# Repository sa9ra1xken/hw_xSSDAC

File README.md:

https://youtube.com/shorts/RJUZ4uOECH0?feature=share

This is a KiCad project for an experimental implementation of a digital audio device that features an XMOS xCORE embedded processor.
The board is intended to behave as a USB audio class output device (USB DAC), or an audio media player (Micro SD card player). 
Please refer to [project Wiki page](https://github.com/sa9ra1xken/hw_xSSDAC/wiki) for more detailed information.

# Development Environment
KiCad7.0. 

### Software project
Software (executable on xCORE-200) for this project is released here (https://github.com/sa9ra1xken/sw_xSSDAC).

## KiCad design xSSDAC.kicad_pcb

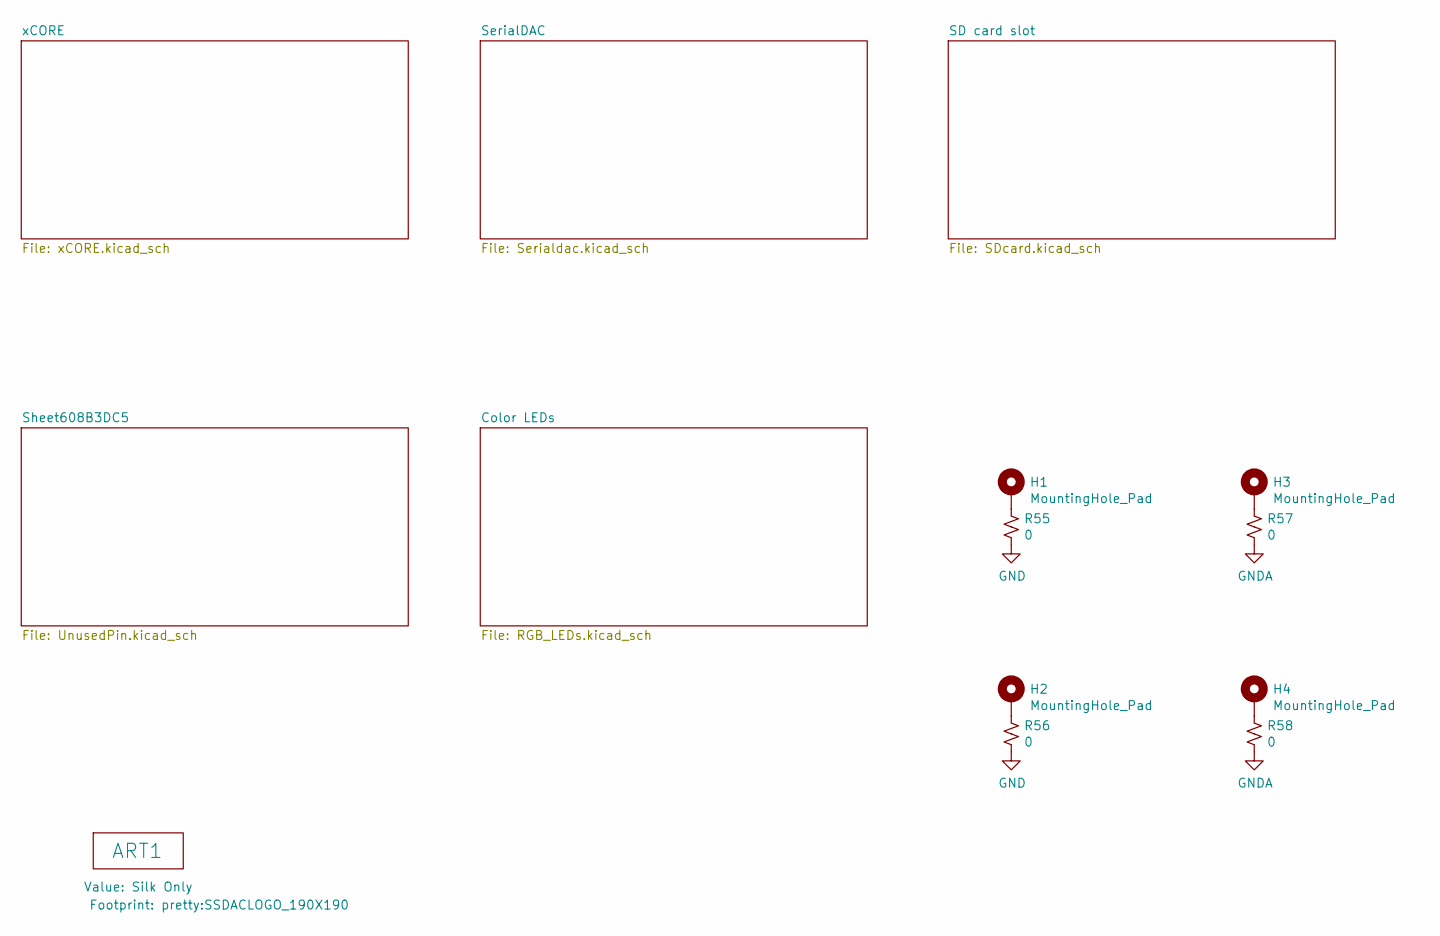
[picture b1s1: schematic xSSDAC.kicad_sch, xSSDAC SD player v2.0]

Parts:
ART1: Silk Only; SSDACLOGO_190X190
H1, H2, H3, H4: MountingHole_Pad; MountingHole_2.7mm_Pad_Via
R55, R56, R57, R58: 0; R_0603_1608Metric_Pad0.98x0.95mm_HandSolder

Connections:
GNDA: R57.2, R58.2; also elsewhere on the board
unnamed: H1.1, R55.1
unnamed: H2.1, R56.1
unnamed: H3.1, R57.1
unnamed: H4.1, R58.1

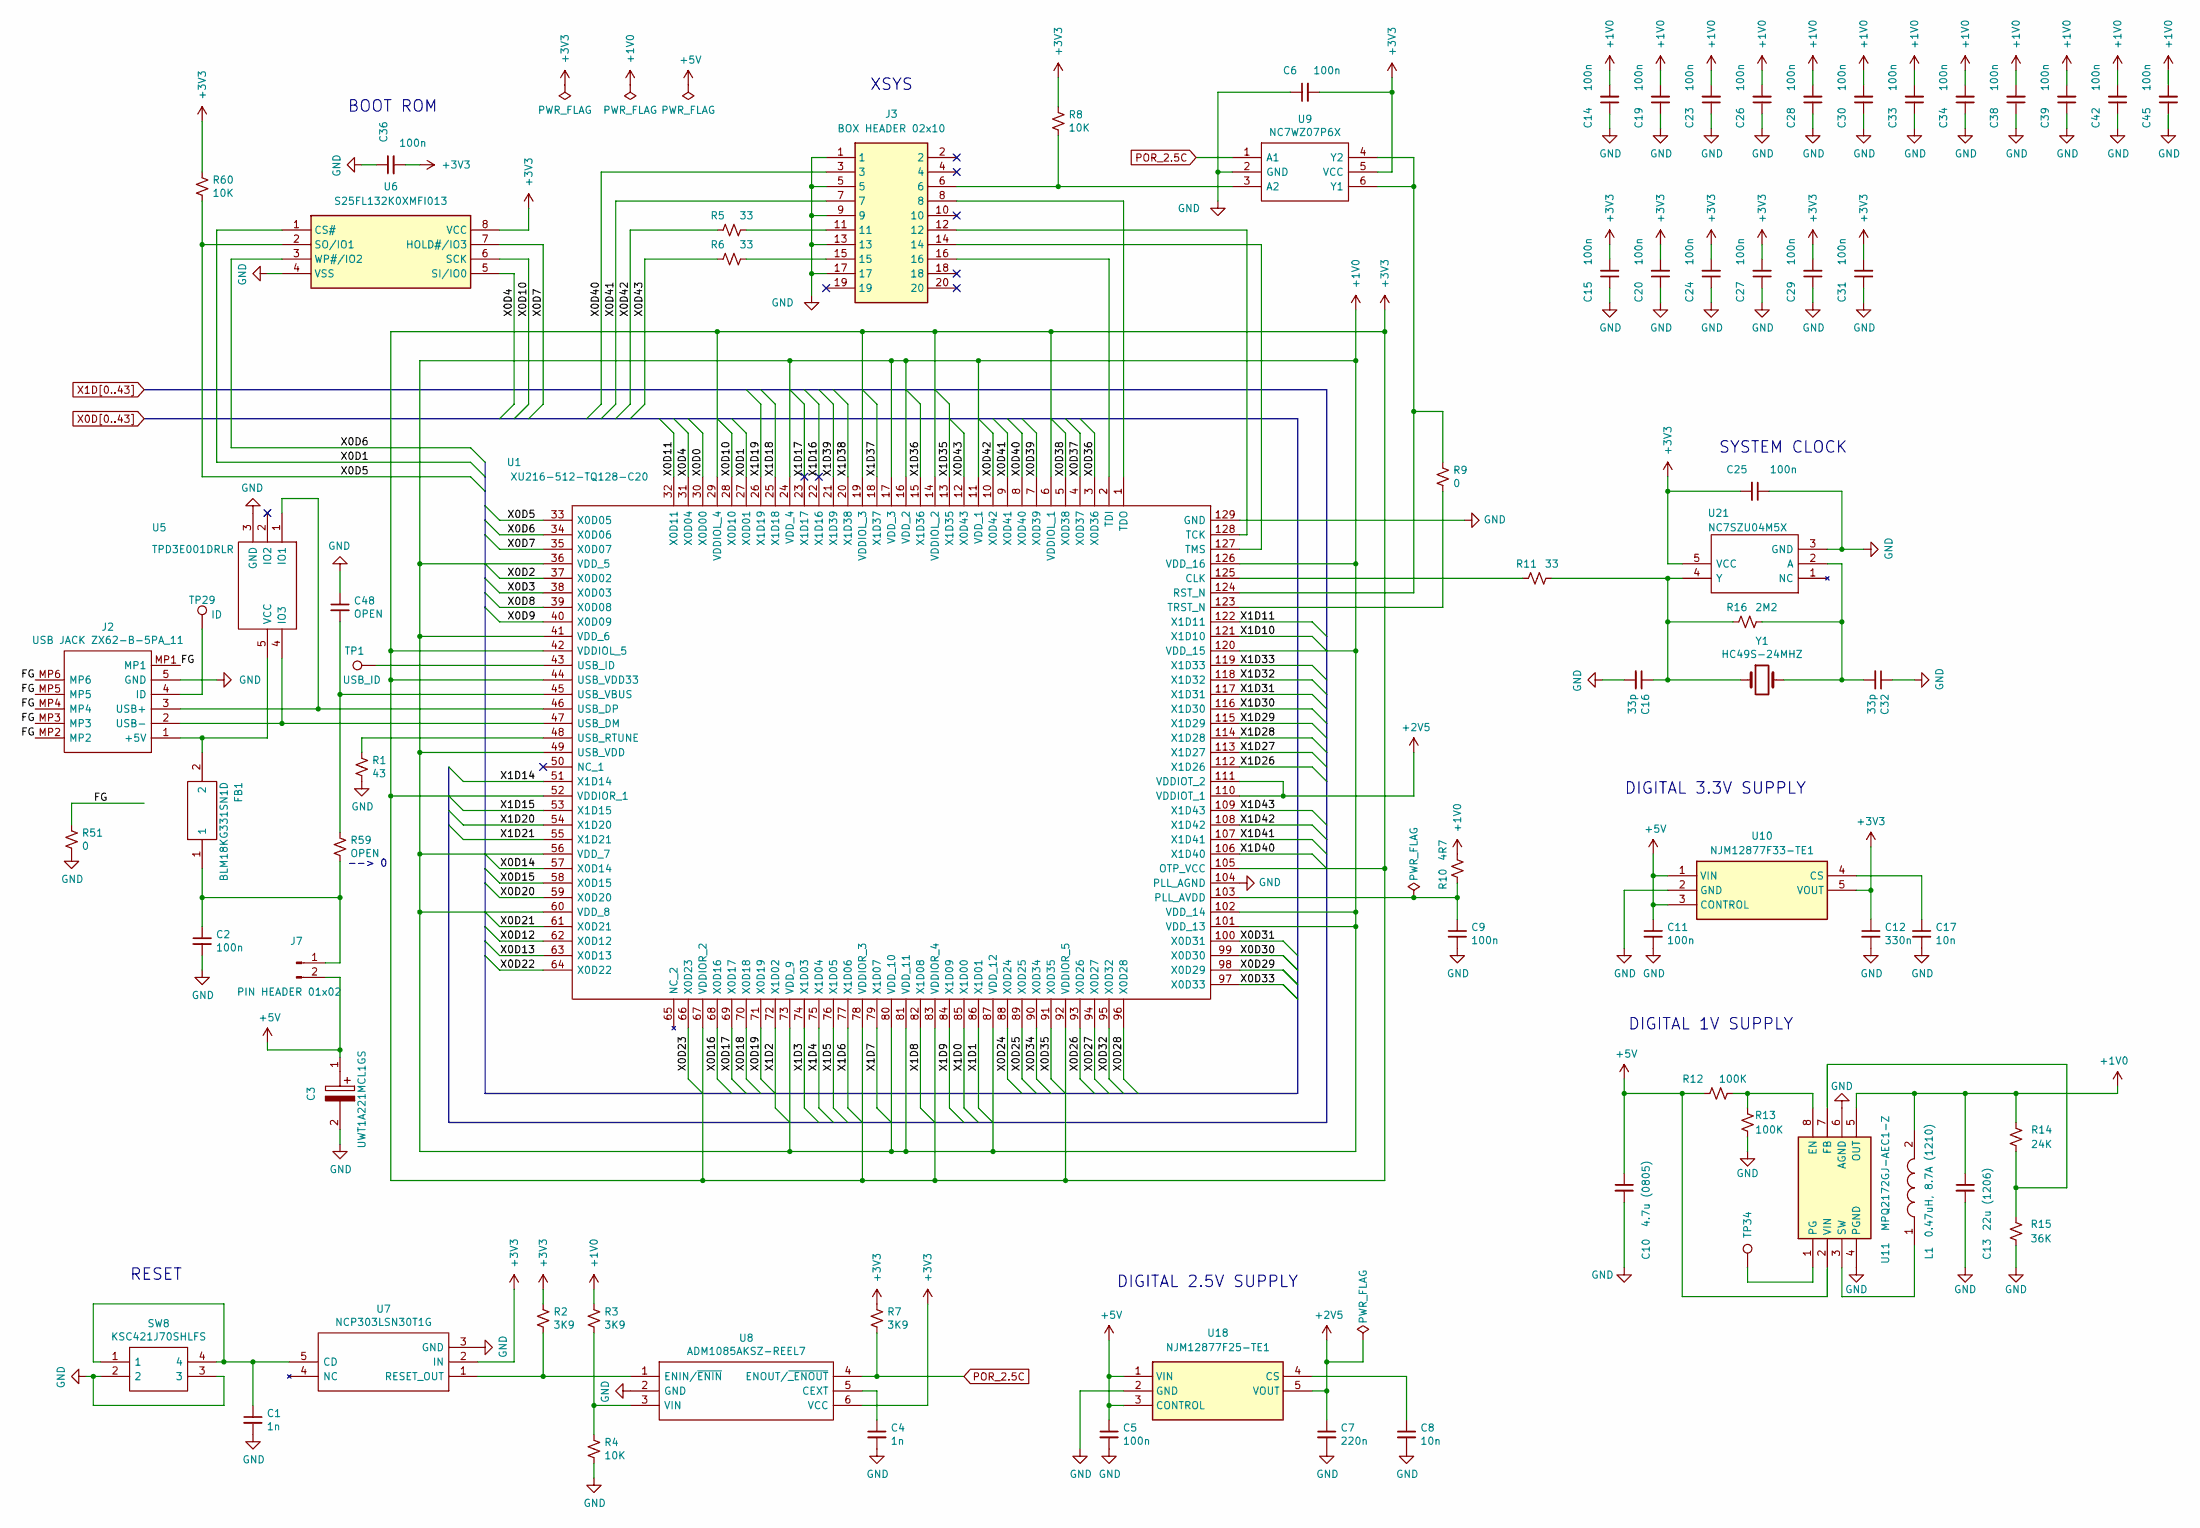
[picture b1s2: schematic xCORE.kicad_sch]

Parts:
C1, C4: 1n; C_0603_1608Metric_Pad1.08x0.95mm_HandSolder
C2, C5, C6, C9, C11, C14, C15, C19, C20, C23, C24, C25, C26, C27, C28, C29, C30, C31, C33, C34, C36, C38, C39, C42, C45: 100n; C_0603_1608Metric_Pad1.08x0.95mm_HandSolder
C3: UWT1A221MCL1GS; CP_Elec_6.3x7.7; Manufacturer_Part_Number UWT1A221MCL1GS; Mouser Part Number 647-UWT1A221MCL1GS
C7: 220n; C_0603_1608Metric_Pad1.08x0.95mm_HandSolder
C8, C17: 10n; C_0603_1608Metric_Pad1.08x0.95mm_HandSolder
C10: 4.7u (0805); C_0805_2012Metric_Pad1.18x1.45mm_HandSolder
C12: 330n; C_0603_1608Metric_Pad1.08x0.95mm_HandSolder
C13: 22u (1206); C_1206_3216Metric_Pad1.33x1.80mm_HandSolder
C16, C32: 33p; C_0603_1608Metric_Pad1.08x0.95mm_HandSolder
C48: OPEN; C_0603_1608Metric_Pad1.08x0.95mm_HandSolder
FB1: BLM18KG331SN1D; BEADC1608X95N; Manufacturer_Part_Number BLM18KG331SN1D; Mouser Part Number 81-BLM18KG331SN1D
J2: USB JACK ZX62-B-5PA_11; ZX62B5PA; Mouser Part Number 798-ZX62-B-5PA11
J3: BOX HEADER 02x10; SHDRRA20W66P254_2X10_3289X986X927P; Manufacturer_Part_Number 5103310-5; Mouser Part Number 571-5103310-5
J7: PIN HEADER 01x02; PinHeader_1x02_P2.54mm_Vertical
L1: 0.47uH, 8.7A (1210); L_1210_3225Metric_Pad1.42x2.65mm_HandSolder; Manufacturer_Part_Number DFE32CAHR47MR0; Mouser Part Number 963-NR10050T4R9N
R1: 43; R_0603_1608Metric_Pad0.98x0.95mm_HandSolder
R2, R3, R7: 3K9; R_0603_1608Metric_Pad0.98x0.95mm_HandSolder
R4, R8, R60: 10K; R_0603_1608Metric_Pad0.98x0.95mm_HandSolder
R5, R6, R11: 33; R_0603_1608Metric_Pad0.98x0.95mm_HandSolder
R9, R51: 0; R_0603_1608Metric_Pad0.98x0.95mm_HandSolder
R10: 4R7; R_0603_1608Metric_Pad0.98x0.95mm_HandSolder
R12, R13: 100K; R_0603_1608Metric_Pad0.98x0.95mm_HandSolder
R14: 24K; R_0603_1608Metric_Pad0.98x0.95mm_HandSolder
R15: 36K; R_0603_1608Metric_Pad0.98x0.95mm_HandSolder
R16: 2M2; R_0603_1608Metric_Pad0.98x0.95mm_HandSolder
R59: OPEN; R_0603_1608Metric_Pad0.98x0.95mm_HandSolder
SW8: KSC421J70SHLFS; KSC401G50SHLFS; Manufacturer_Part_Number KSC421J70SHLFS; Mouser Part Number 611-KSC421J70SHLFS
TP1: USB_ID; TestPoint_Pad_D1.0mm_noCrtYd
TP29: ID; TestPoint_Pad_D1.0mm_noCrtYd
TP34: TestPoint; TestPoint_Pad_D1.0mm_noCrtYd
U1: XU216-512-TQ128-C20; QFP40P1600X1600X120-129N-D; Manufacturer_Part_Number XU216-512-TQ128-C20; DigiKey Part Number 880-1118-ND
U5: TPD3E001DRLR; SOTFL50P160X60-5N; Mouser Part Number 595-TPD3E001DRLR
U6: S25FL132K0XMFI013; SOIC127P800X216-8N; Manufacturer_Part_Number S25FL132K0XMFI013
U7: NCP303LSN30T1G; SOT95P280X145-5N; Manufacturer_Part_Number NCP303LSN30T1G; Mouser Part Number 863-NCP303LSN30T1G
U8: ADM1085AKSZ-REEL7; SOT65P210X110-6N; Manufacturer_Part_Number ADM1085AKSZ-REEL7; Mouser Part Number 584-ADM1085AKSZ-R7
U9: NC7WZ07P6X; SOT65P210X110-6N; Manufacturer_Part_Number NC7WZ07P6X; Mouser Part Number 512-NC7WZ07P6X
U10: NJM12877F33-TE1; SOT-23-5_HandSoldering; Manufacturer_Part_Number NJM12877F33-TE1; Mouser Part Number 513-NJM12877F33-TE1
U11: MPQ2172GJ-AEC1-Z; MPQ2172GJAEC1Z; Manufacturer_Part_Number MPQ2172GJ-AEC1-Z
U18: NJM12877F25-TE1; SOT-23-5_HandSoldering; Manufacturer_Part_Number NJM12877F33-TE1; Mouser Part Number 513-NJM12877F33-TE1
U21: NC7SZU04M5X; SOT95P280X145-5N; Manufacturer_Part_Number NC7SZU04M5X; Mouser Part Number 512-NC7SZU04M5X
Y1: HC49S-24MHZ; Crystal_HC49-U_Vertical; Manufacturer_Part_Number HC49/U-S24000000ABJB

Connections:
+2V5: C7.1, U1.110 (VDDIOT_1), U1.111 (VDDIOT_2), U18.5 (VOUT)
/xCORE/FG: J2.MP1, J2.MP2, J2.MP3, J2.MP4, J2.MP5, J2.MP6, R51.1
unnamed: FB1.2, J2.1 (+5V), U5.5 (VCC)
unnamed: J2.4 (ID), TP29.1
unnamed: J2.3 (USB+), U1.46 (USB_DP), U5.1 (IO1)
unnamed: J2.2 (USB-), U1.47 (USB_DM), U5.4 (IO3)
unnamed: J3.11, R5.1
unnamed: J3.15, R6.1
unnamed: C2.1, FB1.1, J7.1, R59.2
unnamed: R11.2, U1.125 (CLK)
unnamed: C9.1, R10.2, U1.103 (PLL_AVDD)
unnamed: R9.1, U1.124 (RST_N), U9.4 (Y2), U9.6 (Y1)
unnamed: J3.12, U1.128 (TCK)
unnamed: J3.16, U1.2 (TDI)
unnamed: J3.8, U1.1 (TDO)
unnamed: J3.14, U1.127 (TMS)
unnamed: R9.2, U1.123 (TRST_N)
unnamed: TP1.1, U1.43 (USB_ID)
unnamed: R1.1, U1.48 (USB_RTUNE)
unnamed: C48.2, R59.1, U1.45 (USB_VBUS)
unnamed: C1.1, SW8.1, SW8.4, U7.5 (CD)
unnamed: R2.2, U7.1 (RESET_OUT), U8.1 (ENIN/~ENIN)
unnamed: C4.1, U8.5 (CEXT)
unnamed: R3.2, R4.1, U8.3 (VIN)
unnamed: J3.6, R8.2, U9.3 (A2)
unnamed: C17.1, U10.4 (CS)
unnamed: R12.2, R13.2, U11.8 (EN)
unnamed: R14.2, R15.2, U11.7 (FB)
unnamed: L1.1, U11.3 (SW)
unnamed: C8.1, U18.4 (CS)
unnamed: C32.2, R16.1, U21.2 (A), Y1.2
unnamed: C16.1, R11.1, R16.2, U21.4 (Y), Y1.1
POR_2.5C: R7.2, U8.4 (ENOUT/~_ENOUT), U9.1 (A1)
X0D0: U1.30 (X0D00); also elsewhere on the board
X0D1: U1.27 (X0D01), U6.1 (CS#)
X0D2: U1.37 (X0D02); also elsewhere on the board
X0D3: U1.38 (X0D03); also elsewhere on the board
X0D4: U1.31 (X0D04), U6.5 (SI/IO0)
X0D5: R60.2, U1.33 (X0D05), U6.2 (SO/IO1)
X0D6: U1.34 (X0D06), U6.3 (WP#/IO2)
X0D7: U1.35 (X0D07), U6.7 (HOLD#/IO3)
X0D8: U1.39 (X0D08); also elsewhere on the board
X0D9: U1.40 (X0D09); also elsewhere on the board
X0D10: U1.28 (X0D10), U6.6 (SCK)
X0D11: U1.32 (X0D11); also elsewhere on the board
X0D12: U1.62 (X0D12); also elsewhere on the board
X0D13: U1.63 (X0D13); also elsewhere on the board
X0D14: U1.57 (X0D14); also elsewhere on the board
X0D15: U1.58 (X0D15); also elsewhere on the board
X0D16: U1.68 (X0D16); also elsewhere on the board
X0D17: U1.69 (X0D17); also elsewhere on the board
X0D18: U1.70 (X0D18); also elsewhere on the board
X0D19: U1.71 (X0D19); also elsewhere on the board
X0D20: U1.59 (X0D20); also elsewhere on the board
X0D21: U1.61 (X0D21); also elsewhere on the board
X0D22: U1.64 (X0D22); also elsewhere on the board
X0D23: U1.66 (X0D23); also elsewhere on the board
X0D26: U1.93 (X0D26); also elsewhere on the board
X0D27: U1.94 (X0D27); also elsewhere on the board
X0D28: U1.96 (X0D28); also elsewhere on the board
X0D29: U1.98 (X0D29); also elsewhere on the board
X0D30: U1.99 (X0D30); also elsewhere on the board
X0D31: U1.100 (X0D31); also elsewhere on the board
X0D32: U1.95 (X0D32); also elsewhere on the board
X0D33: U1.97 (X0D33); also elsewhere on the board
X0D34: U1.90 (X0D34); also elsewhere on the board
X0D35: U1.91 (X0D35); also elsewhere on the board
X0D36: U1.3 (X0D36); also elsewhere on the board
X0D37: U1.4 (X0D37); also elsewhere on the board
X0D38: U1.5 (X0D38); also elsewhere on the board
X0D39: U1.7 (X0D39); also elsewhere on the board
X0D40: J3.3, U1.8 (X0D40)
X0D41: J3.7, U1.9 (X0D41)
X0D42: R5.2, U1.10 (X0D42)
X0D43: R6.2, U1.12 (X0D43)
X1D0: U1.85 (X1D00); also elsewhere on the board
X1D1: U1.86 (X1D01); also elsewhere on the board
X1D2: U1.72 (X1D02); also elsewhere on the board
X1D3: U1.74 (X1D03); also elsewhere on the board
X1D4: U1.75 (X1D04); also elsewhere on the board
X1D5: U1.76 (X1D05)
X1D6: U1.77 (X1D06)
X1D7: U1.79 (X1D07)
X1D8: U1.82 (X1D08); also elsewhere on the board
X1D9: U1.84 (X1D09); also elsewhere on the board
X1D10: U1.121 (X1D10); also elsewhere on the board
X1D11: U1.122 (X1D11); also elsewhere on the board
X1D14: U1.51 (X1D14)
X1D15: U1.53 (X1D15)
X1D16: U1.22 (X1D16)
X1D17: U1.23 (X1D17)
X1D18: U1.25 (X1D18)
X1D19: U1.26 (X1D19)
X1D20: U1.54 (X1D20)
X1D21: U1.55 (X1D21)
X1D26: U1.112 (X1D26); also elsewhere on the board
X1D27: U1.113 (X1D27); also elsewhere on the board
X1D28: U1.114 (X1D28); also elsewhere on the board
X1D29: U1.115 (X1D29); also elsewhere on the board
X1D30: U1.116 (X1D30); also elsewhere on the board
X1D31: U1.117 (X1D31); also elsewhere on the board
X1D32: U1.118 (X1D32); also elsewhere on the board
X1D33: U1.119 (X1D33); also elsewhere on the board
X1D35: U1.13 (X1D35); also elsewhere on the board
X1D36: U1.15 (X1D36); also elsewhere on the board
X1D37: U1.18 (X1D37); also elsewhere on the board
X1D38: U1.20 (X1D38); also elsewhere on the board
X1D39: U1.21 (X1D39); also elsewhere on the board
X1D40: U1.106 (X1D40); also elsewhere on the board
X1D41: U1.107 (X1D41); also elsewhere on the board
X1D42: U1.108 (X1D42); also elsewhere on the board
X1D43: U1.109 (X1D43); also elsewhere on the board

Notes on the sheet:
DIGITAL 3.3V SUPPLY
--> 0
DIGITAL 2.5V SUPPLY
XSYS
DIGITAL 1V SUPPLY
BOOT ROM
SYSTEM CLOCK
RESET

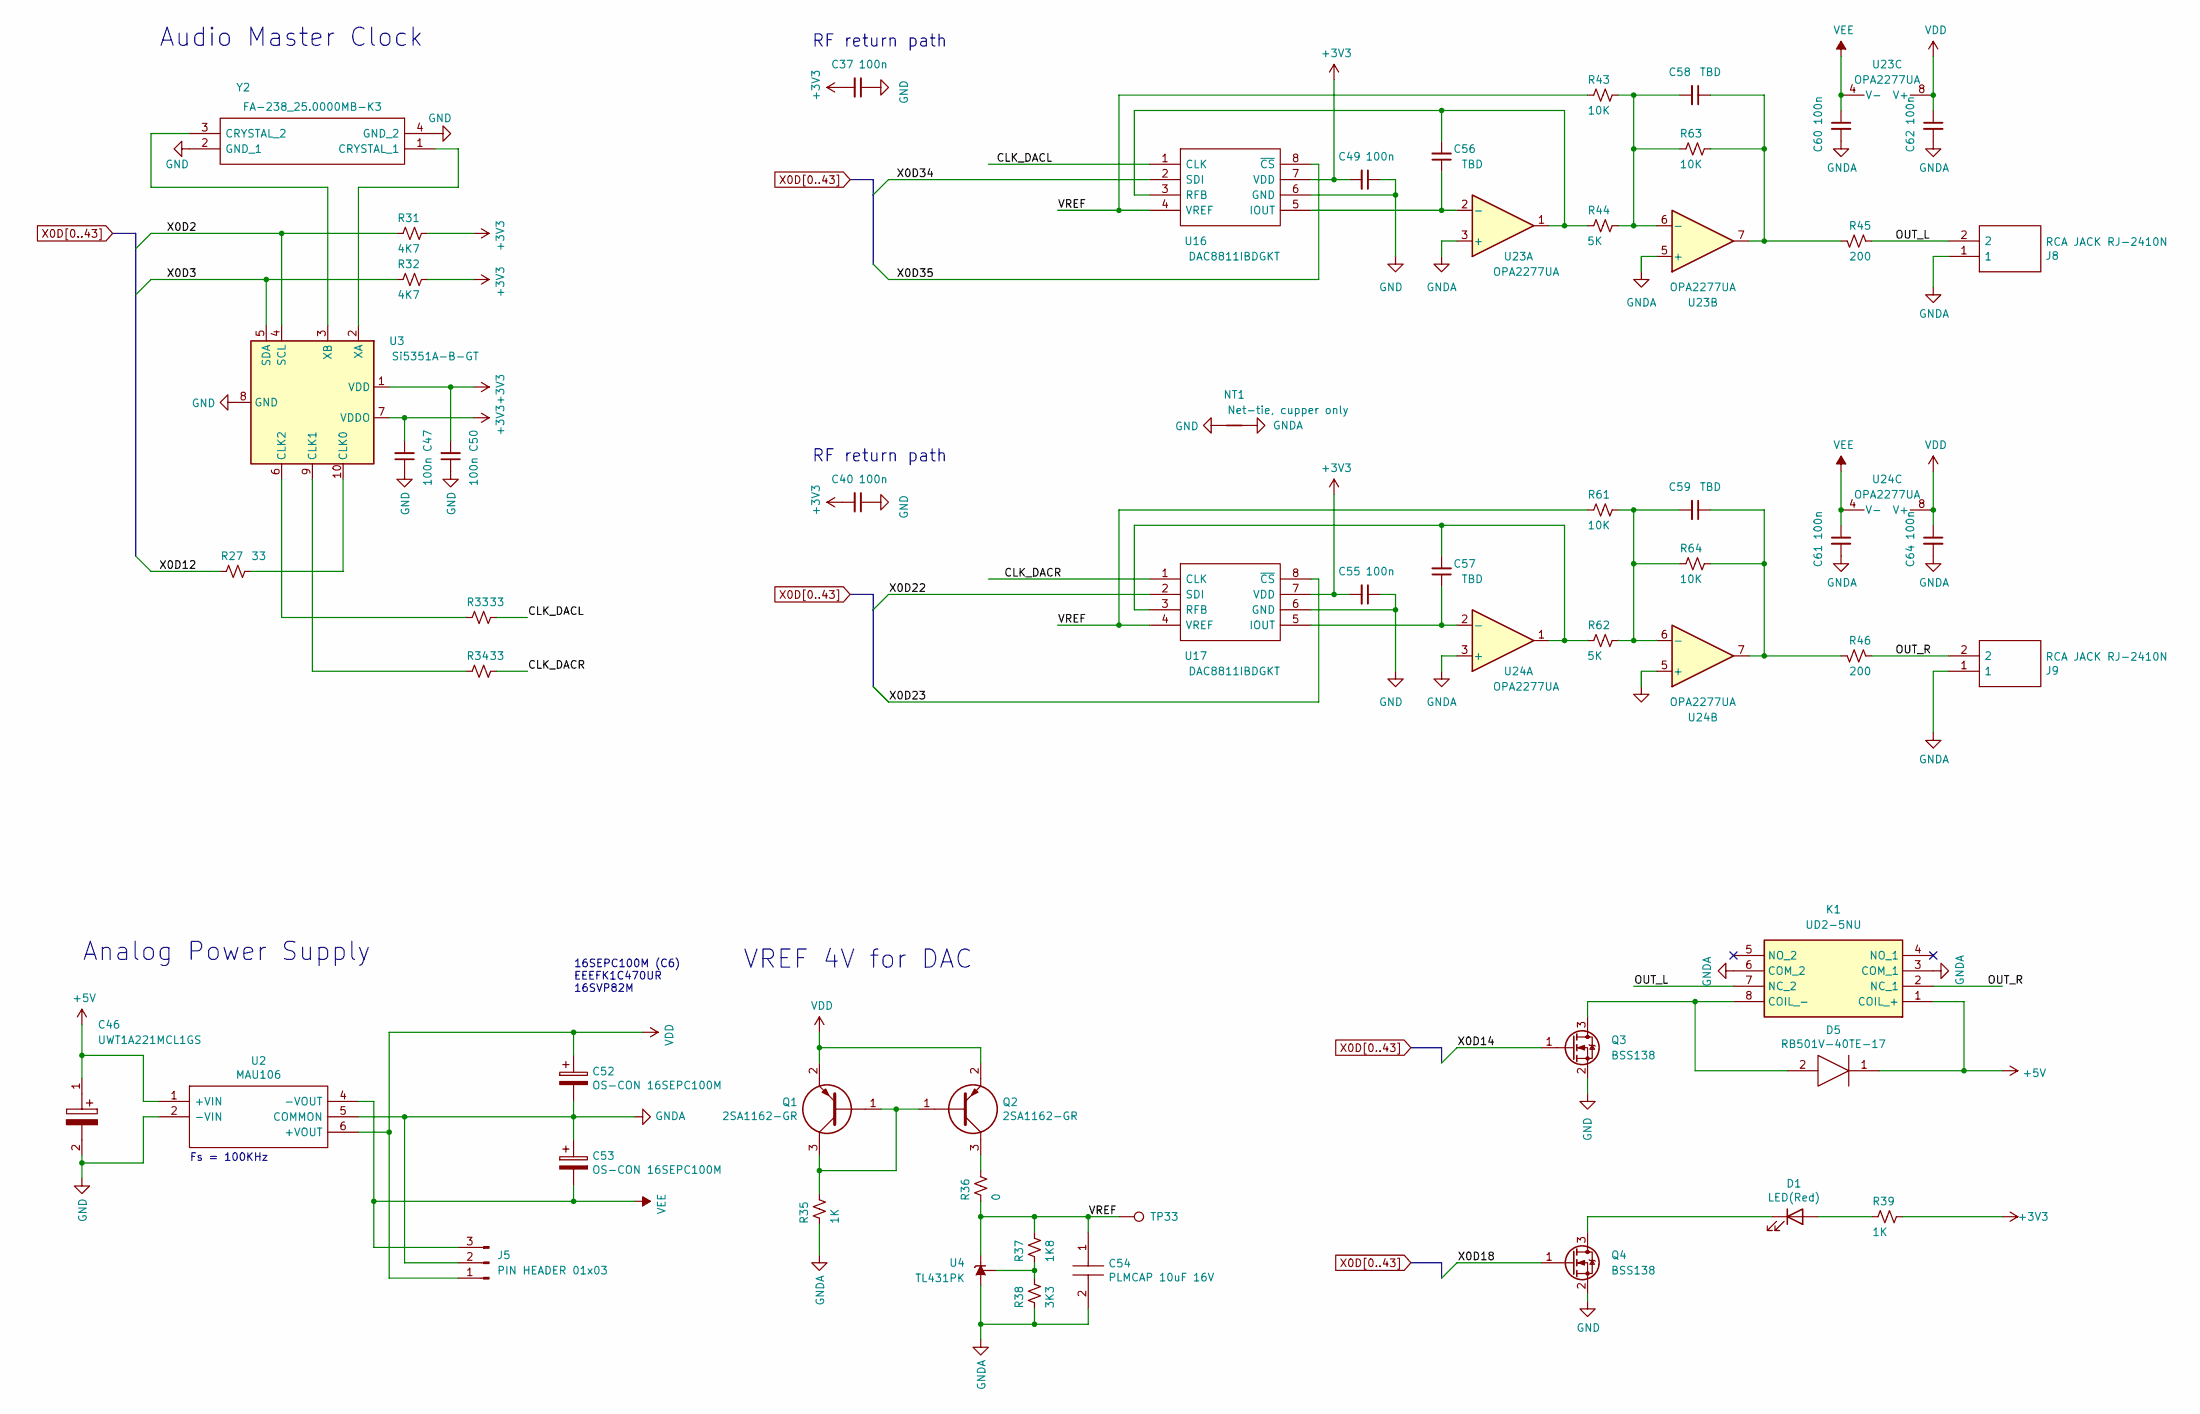
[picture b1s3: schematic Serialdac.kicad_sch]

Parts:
C37, C40, C47, C49, C50, C55, C60, C61, C62, C64: 100n; C_0603_1608Metric_Pad1.08x0.95mm_HandSolder
C46: UWT1A221MCL1GS; CP_Elec_6.3x7.7; Manufacturer_Part_Number UWT1A221MCL1GS; Mouser Part Number 647-UWT1A221MCL1GS
C52, C53: OS-CON 16SEPC100M; CP_Radial_D6.3mm_P2.50mm; Manufacturer_Part_Number OS-CON 16SEPC100M
C54: PLMCAP 10uF 16V; CAPC4532X280N; Manufacturer_Part_Number 16MU106MC44532; Mouser Part Number 232-16MU106MC44532
C56, C57, C58, C59: TBD; C_Rect_L4.0mm_W2.5mm_P2.50mm
D1: LED(Red); LED_0603_1608Metric_Pad1.05x0.95mm_HandSolder; Manufacturer_Part_Number OSHR1608C1A
D5: RB501V-40TE-17; SODFL2512X90N; Manufacturer_Part_Number RB501V-40TE-17; Mouser Part Number 755-RB501V-40TE-17
J5: PIN HEADER 01x03; PinHeader_1x03_P2.54mm_Vertical
J8, J9: RCA JACK RJ-2410N; RJ2410N; Manufacturer_Part_Number RJ-2410N
K1: UD2-5NU; UD25NUN; Manufacturer_Part_Number UD2-5NU; Mouser Part Number 551-UD2-5NU
NT1: Net-tie, cupper only; NetTie-2_SMD_Pad1.0mm
Q1, Q2: 2SA1162-GR; SC-59; Manufacturer_Part_Number 2SA1162-GR(F)
Q3, Q4: BSS138; SOT-23; Manufacturer_Part_Number BSS138
R27, R33, R34: 33; R_0603_1608Metric_Pad0.98x0.95mm_HandSolder
R31, R32: 4K7; R_0603_1608Metric_Pad0.98x0.95mm_HandSolder
R35, R39: 1K; R_0603_1608Metric_Pad0.98x0.95mm_HandSolder
R36: 0; R_0603_1608Metric_Pad0.98x0.95mm_HandSolder
R37: 1K8; R_0603_1608Metric_Pad0.98x0.95mm_HandSolder
R38: 3K3; R_0603_1608Metric_Pad0.98x0.95mm_HandSolder
R43, R61, R63, R64: 10K; R_Axial_DIN0204_L3.6mm_D1.6mm_P2.54mm_Vertical
R44, R62: 5K; R_Axial_DIN0204_L3.6mm_D1.6mm_P2.54mm_Vertical
R45, R46: 200; R_Axial_DIN0204_L3.6mm_D1.6mm_P2.54mm_Vertical
TP33: TestPoint; TestPoint_Pad_3.0x3.0mm
U2: MAU106; MAU109; Manufacturer_Part_Number MAU106
U3: Si5351A-B-GT; SOP50P490X110-10N; Manufacturer_Part_Number Si5351A-B-GT
U4: TL431PK; SOT-89-3; Manufacturer_Part_Number TA76431F
U16, U17: DAC8811IBDGKT; TSSOP-8_3x3mm_P0.65mm; Manufacturer_Part_Number DAC8811IBDGKT
U23, U24: OPA2277UA; SOIC-8_3.9x4.9mm_P1.27mm; Manufacturer_Part_Number OPA2277UA
Y2: FA-238_25.0000MB-K3; EPSON-FA-238; Manufacturer_Part_Number FA-238 25.0000MB-K3; Mouser Part Number 732-FA238-25B-K3

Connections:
/SerialDAC/CLK_DACL: R33.1, U16.1 (CLK)
/SerialDAC/CLK_DACR: R34.1, U17.1 (CLK)
/SerialDAC/OUT_L: J8.2, K1.7 (NC_2), R45.2
/SerialDAC/OUT_R: J9.2, K1.2 (NC_1), R46.2
GNDA: C52.2, C53.1, C54.2, C60.2, C61.2, C62.2, C64.2, J5.2, J8.1, J9.1, K1.3 (COM_1), K1.6 (COM_2), NT1.2, R35.2, R38.2, U2.5 (COMMON), U4.2 (A), U23.3 (+), U23.5 (+), U24.3 (+), U24.5 (+); also elsewhere on the board
unnamed: C58.1, R45.1, R63.2, U23.7
unnamed: C59.1, R46.1, R64.2, U24.7
unnamed: D5.2, K1.8 (COIL_-), Q3.3 (D)
unnamed: Q1.1, Q1.3, Q2.1, R35.1
unnamed: Q2.3, R36.1
unnamed: R27.1, U3.10 (CLK0)
unnamed: R34.2, U3.9 (CLK1)
unnamed: R33.2, U3.6 (CLK2)
unnamed: U3.2 (XA), Y2.1 (CRYSTAL_1)
unnamed: U3.3 (XB), Y2.3 (CRYSTAL_2)
unnamed: R37.2, R38.1, U4.1 (REF)
unnamed: C56.1, U16.5 (IOUT), U23.2 (-)
unnamed: C56.2, R44.1, U16.3 (RFB), U23.1
unnamed: C57.1, U17.5 (IOUT), U24.2 (-)
unnamed: C57.2, R62.1, U17.3 (RFB), U24.1
unnamed: C58.2, R43.2, R44.2, R63.1, U23.6 (-)
unnamed: C59.2, R61.2, R62.2, R64.1, U24.6 (-)
VDD: C52.1, C62.1, C64.1, J5.1, Q1.2, Q2.2, U2.6 (+VOUT), U23.8 (V+), U24.8 (V+)
VEE: C53.2, C60.1, C61.1, J5.3, U2.4 (-VOUT), U23.4 (V-), U24.4 (V-)
X0D2: R31.2, U3.4 (SCL); also elsewhere on the board
X0D3: R32.2, U3.5 (SDA); also elsewhere on the board
X0D12: R27.2; also elsewhere on the board
X0D14: Q3.1 (G); also elsewhere on the board
X0D22: U17.2 (SDI); also elsewhere on the board
X0D23: U17.8 (~CS); also elsewhere on the board
X0D34: U16.2 (SDI); also elsewhere on the board
X0D35: U16.8 (~CS); also elsewhere on the board

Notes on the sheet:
Fs = 100KHz
RF return path
VREF 4V for DAC
16SEPC100M (C6) EEEFK1C470UR 16SVP82M
Analog Power Supply
Audio Master Clock

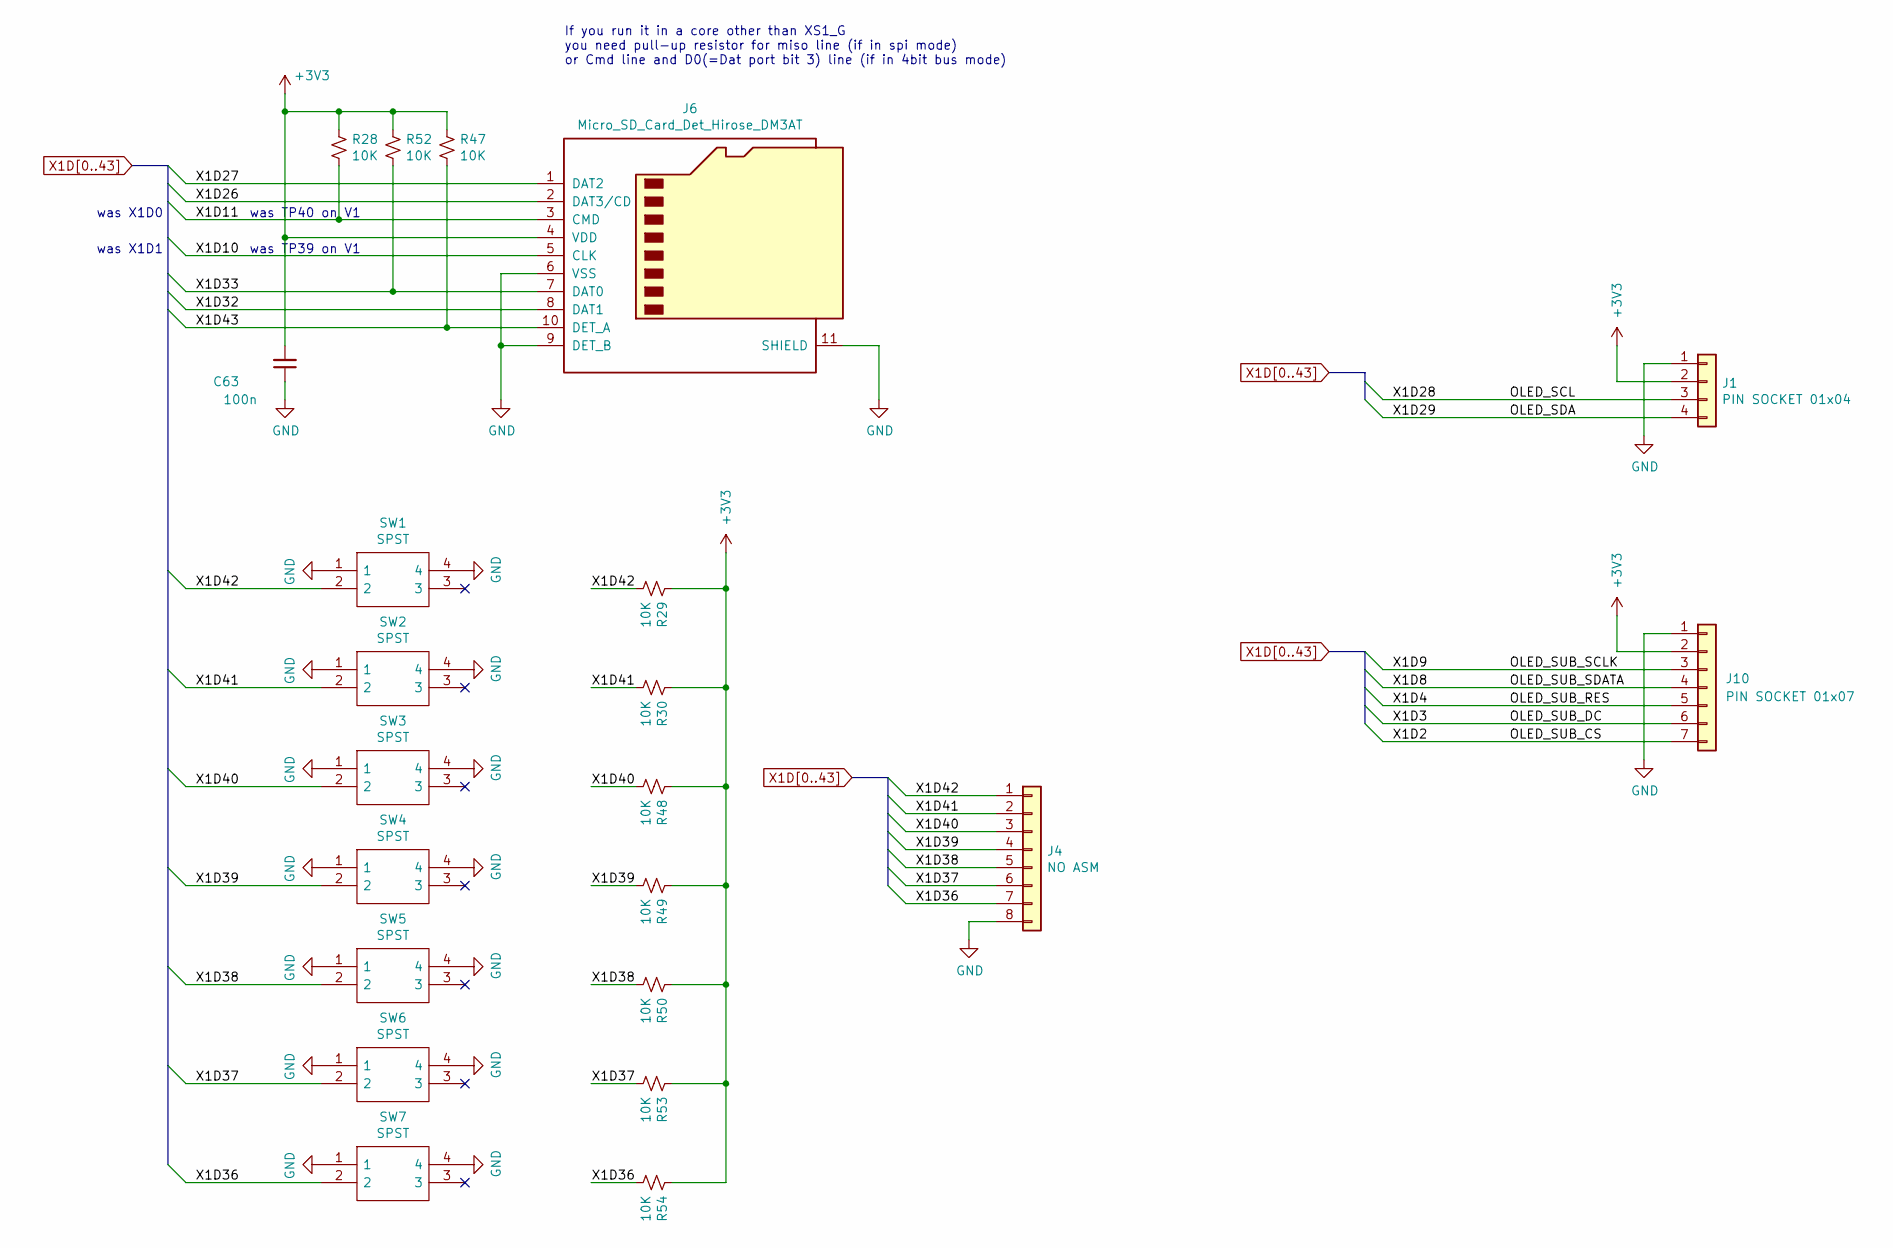
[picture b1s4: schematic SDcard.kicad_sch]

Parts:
C63: 100n; C_0603_1608Metric_Pad1.08x0.95mm_HandSolder
J1: PIN SOCKET 01x04; OLED_4pin_1.3_128X64
J4: NO ASM; PinHeader_1x08_P2.54mm_Vertical
J6: Micro_SD_Card_Det_Hirose_DM3AT; Hirose_DM3AT-SF-PEJM5
J10: PIN SOCKET 01x07; OLED_7pin_0.95_96X64_RGB
R28, R29, R30, R47, R48, R49, R50, R52, R53, R54: 10K; R_0603_1608Metric_Pad0.98x0.95mm_HandSolder
SW1, SW4, SW7: SPST; TS-0606; Manufacturer_Part_Number DTS-63-N-V-RED
SW2, SW3, SW5, SW6: SPST; TS-0606; Manufacturer_Part_Number DTS-63-N-V-WHT

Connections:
X1D2: J10.7; also elsewhere on the board
X1D3: J10.6; also elsewhere on the board
X1D4: J10.5; also elsewhere on the board
X1D8: J10.4; also elsewhere on the board
X1D9: J10.3; also elsewhere on the board
X1D10: J6.5 (CLK); also elsewhere on the board
X1D11: J6.3 (CMD), R28.2; also elsewhere on the board
X1D26: J6.2 (DAT3/CD); also elsewhere on the board
X1D27: J6.1 (DAT2); also elsewhere on the board
X1D28: J1.3; also elsewhere on the board
X1D29: J1.4; also elsewhere on the board
X1D32: J6.8 (DAT1); also elsewhere on the board
X1D33: J6.7 (DAT0), R52.2; also elsewhere on the board
X1D36: J4.7, R54.2, SW7.2; also elsewhere on the board
X1D37: J4.6, R53.2, SW6.2; also elsewhere on the board
X1D38: J4.5, R50.2, SW5.2; also elsewhere on the board
X1D39: J4.4, R49.2, SW4.2; also elsewhere on the board
X1D40: J4.3, R48.2, SW3.2; also elsewhere on the board
X1D41: J4.2, R30.2, SW2.2; also elsewhere on the board
X1D42: J4.1, R29.2, SW1.2; also elsewhere on the board
X1D43: J6.10 (DET_A), R47.2; also elsewhere on the board

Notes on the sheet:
was X1D0
was X1D1
was TP40 on V1
was TP39 on V1
If you run it in a core other than XS1_G you need pull-up resistor for miso line (if in spi mode) or Cmd line and D0(=Dat port bit 3) line (if in 4bit bus mode)

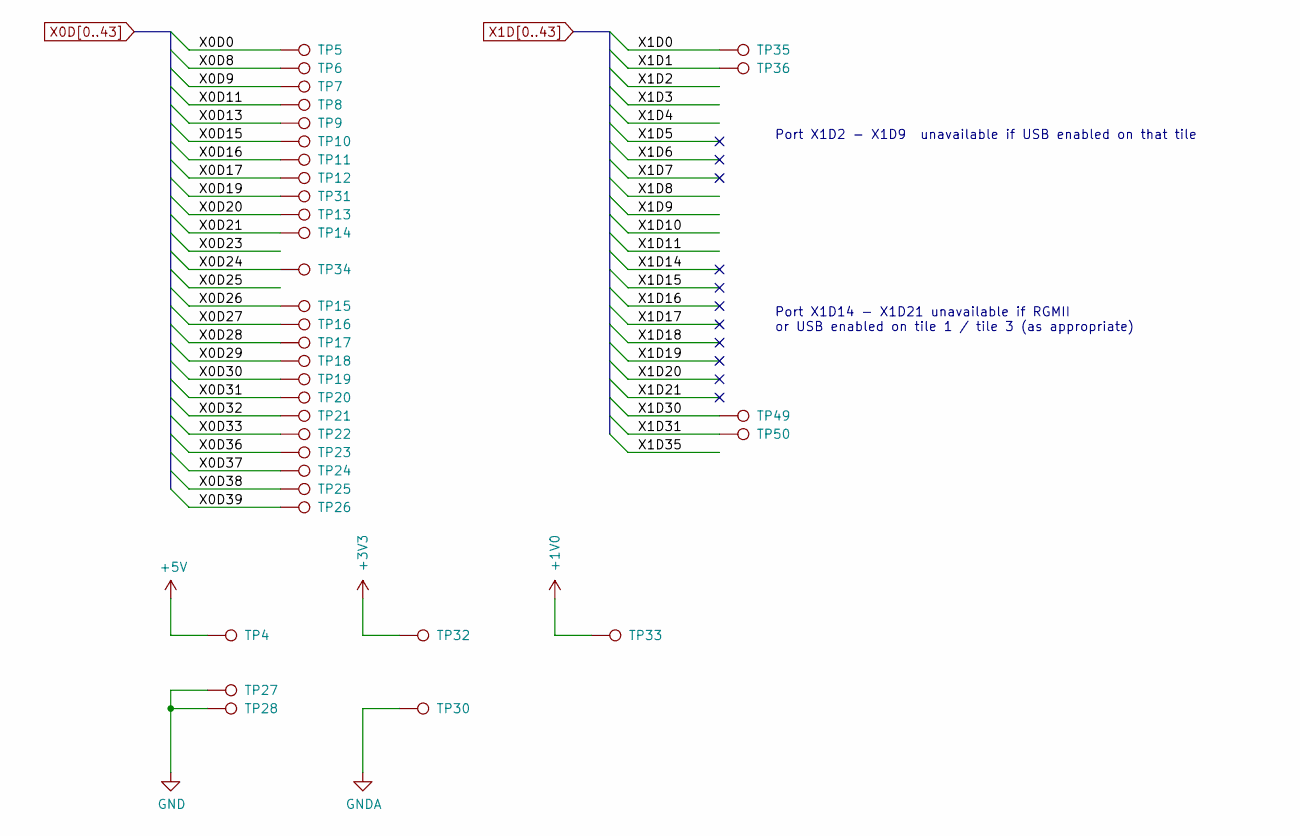
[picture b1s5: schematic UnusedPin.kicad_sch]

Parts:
TP4, TP27, TP28, TP30, TP32, TP33: TestPoint; TestPoint_Pad_3.0x3.0mm
TP5, TP6, TP7, TP8, TP9, TP10, TP11, TP12, TP13, TP14, TP15, TP16, TP17, TP18, TP19, TP20, TP21, TP22, TP23, TP24, TP25, TP26, TP31, TP34, TP35, TP36, TP49, TP50: TestPoint; TestPoint_Pad_D1.0mm_noCrtYd

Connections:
GNDA: TP30.1; also elsewhere on the board
X0D0: TP5.1; also elsewhere on the board
X0D8: TP6.1; also elsewhere on the board
X0D9: TP7.1; also elsewhere on the board
X0D11: TP8.1; also elsewhere on the board
X0D13: TP9.1; also elsewhere on the board
X0D15: TP10.1; also elsewhere on the board
X0D16: TP11.1; also elsewhere on the board
X0D17: TP12.1; also elsewhere on the board
X0D19: TP31.1; also elsewhere on the board
X0D20: TP13.1; also elsewhere on the board
X0D21: TP14.1; also elsewhere on the board
X0D26: TP15.1; also elsewhere on the board
X0D27: TP16.1; also elsewhere on the board
X0D28: TP17.1; also elsewhere on the board
X0D29: TP18.1; also elsewhere on the board
X0D30: TP19.1; also elsewhere on the board
X0D31: TP20.1; also elsewhere on the board
X0D32: TP21.1; also elsewhere on the board
X0D33: TP22.1; also elsewhere on the board
X0D36: TP23.1; also elsewhere on the board
X0D37: TP24.1; also elsewhere on the board
X0D38: TP25.1; also elsewhere on the board
X0D39: TP26.1; also elsewhere on the board
X1D0: TP35.1; also elsewhere on the board
X1D1: TP36.1; also elsewhere on the board
X1D30: TP49.1; also elsewhere on the board
X1D31: TP50.1; also elsewhere on the board

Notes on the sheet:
Port X1D2 - X1D9 unavailable if USB enabled on that tile
Port X1D14 - X1D21 unavailable if RGMII or USB enabled on tile 1 / tile 3 (as appropriate)

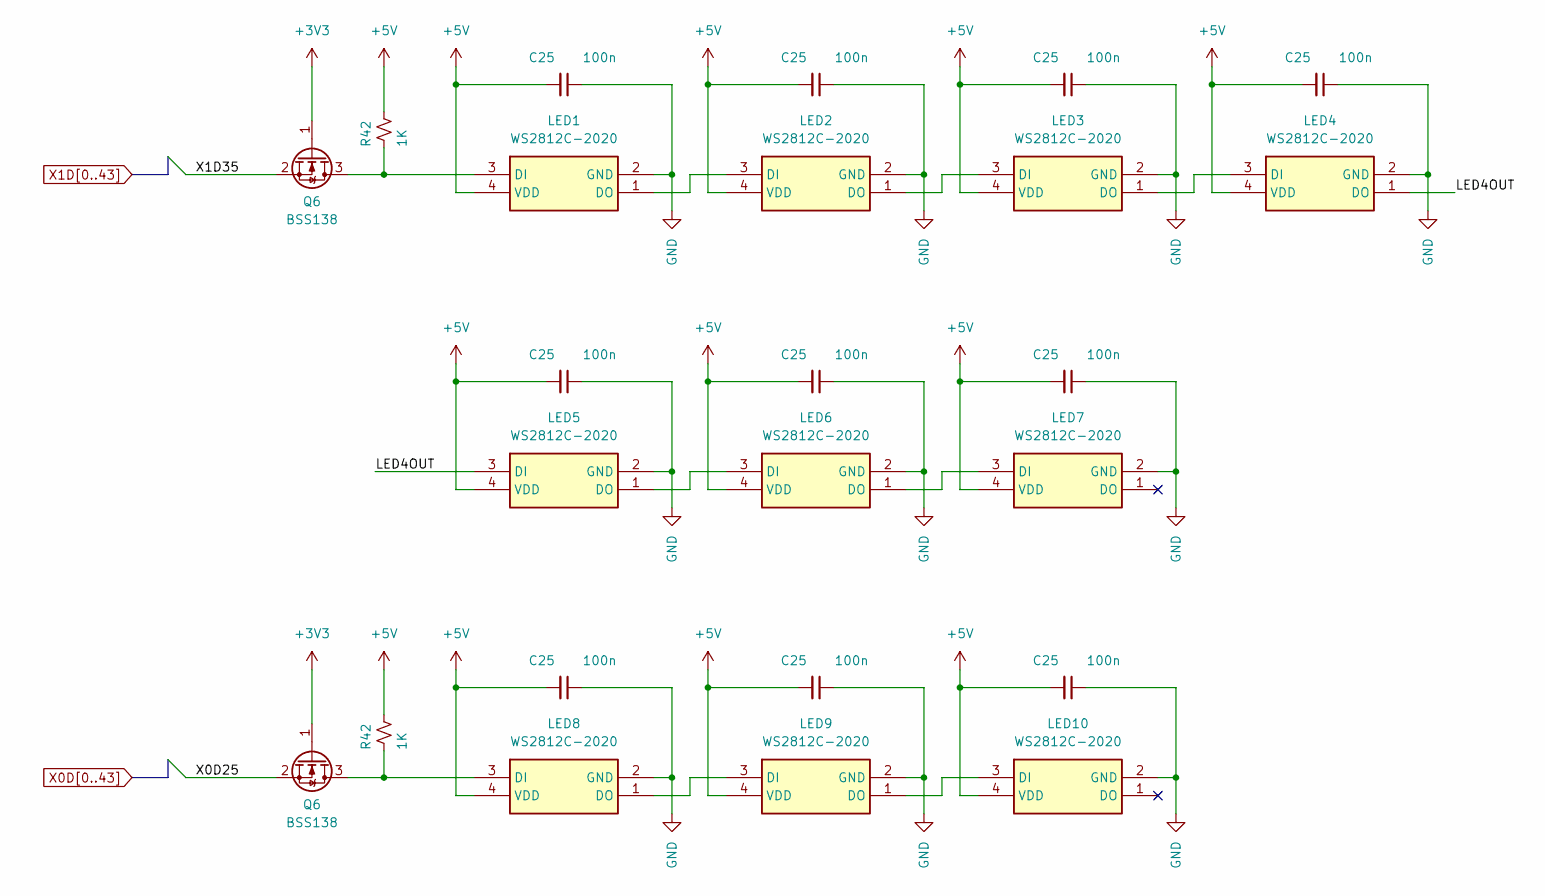
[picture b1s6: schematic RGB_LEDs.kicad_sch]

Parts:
C25: 100n; C_0603_1608Metric_Pad1.08x0.95mm_HandSolder
LED1, LED2, LED3, LED4, LED5, LED6, LED7, LED8, LED9, LED10: WS2812C-2020; WS2812C2020; Manufacturer_Part_Number WS2812C-2020
Q6: BSS138; SOT-23; Manufacturer_Part_Number BSS138
R42: 1K; R_0603_1608Metric_Pad0.98x0.95mm_HandSolder

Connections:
/Color LEDs/LED4OUT: LED4.1 (DO), LED5.3 (DI)
unnamed: LED1.1 (DO), LED2.3 (DI)
unnamed: LED2.1 (DO), LED3.3 (DI)
unnamed: LED3.1 (DO), LED4.3 (DI)
unnamed: LED5.1 (DO), LED6.3 (DI)
unnamed: LED6.1 (DO), LED7.3 (DI)
unnamed: LED8.1 (DO), LED9.3 (DI)
unnamed: LED9.1 (DO), LED10.3 (DI)
X0D18: Q6.1 (G); also elsewhere on the board

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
